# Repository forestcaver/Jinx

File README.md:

# Jinx

Eurorack 0603 triple S&amp;H in 4hp (based on the S&H section of Mutable Instruments Kinks module)

I have deleted the BoM which contained Mouser part numbers etc. as, despite requests here, I was receiveing far too many requests for part substitutions and advice on the BoM and build. Apologies to those who found it useful, but you can generate one from Eagle.

I have also deleted the gerber files as I also had complaints that they did not include the information that some people wanted (I generate a minimal silkscreen as I find on dense boards that a crowded silkscreen is confusing. As I am building just for me I don't think that is unreasonable. Also, it is trivial to generate gerbers with whatever information you need. So, to try to reduce the number of messages I receive about this, I have deleted them. Apologies to those who found them useful.

**** Please note - pcbs and panels are being sold by other people - I have no connection, financial or otherwise, to anyone selling pcbs and panels, hence I feel no commercial obligation to offer build support! I am just freely offering up these designs! Enjoy! ****

cc-by-sa-3.0

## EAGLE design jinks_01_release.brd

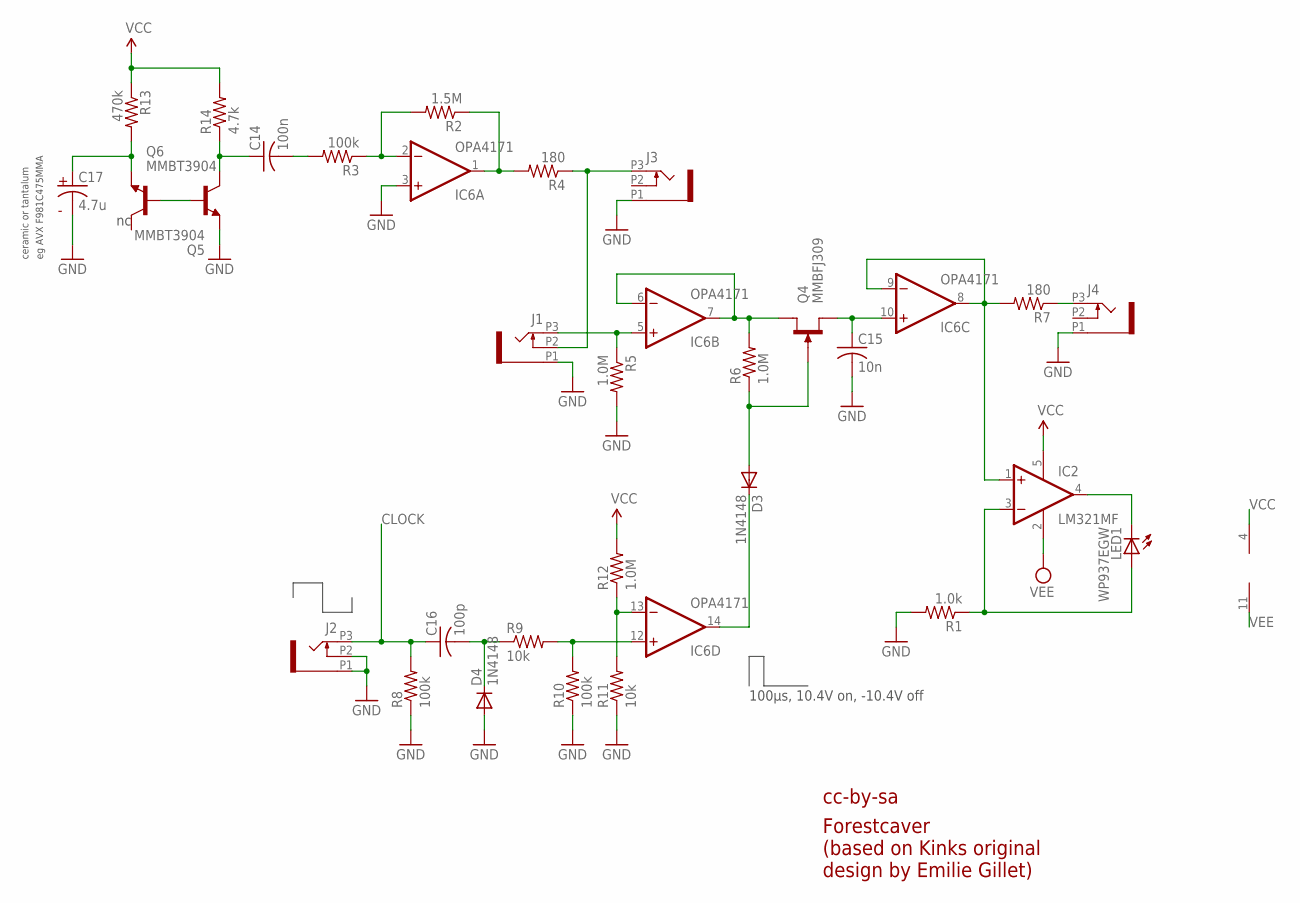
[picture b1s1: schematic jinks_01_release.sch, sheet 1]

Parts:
C14: 100n; C0603
C15: 10n; C0603
C16: 100p; C0603
C17: 4.7u; C0603
D3, D4: 1N4148; SOD523
IC2: LM321MF; SOT23-5
IC6: OPA4171; TSSOP14
J1, J2, J3, J4: PJ301_THONKICONN6; WQP_PJ_301M6
LED1: WP937EGW; LED3MM
Q4: MMBFJ309; SOT23
Q5, Q6: MMBT3904; SOT23-BEC
R1: 1.0k; R0603
R2: 1.5M; R0603
R3, R8, R10: 100k; R0603
R4, R7: 180; R0603
R5, R6, R12: 1.0M; R0603
R9, R11: 10k; R0603
R13: 470k; R0603
R14: 4.7k; R0603

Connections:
CLOCK: C16.1, J2.P3 (3), R8.2; also elsewhere on the board
GND: C15.2, C17.2, D4.A, IC6.3 (+IN), J1.P1 (1), J2.P1 (1), J2.P2 (2), J3.P1 (1), J4.P1 (1), Q6.E, R1.2, R5.2, R8.1, R10.1, R11.1; also elsewhere on the board
unnamed: IC2.4 (OUT), LED1.K (C)
unnamed: IC2.3 (-IN), LED1.A, R1.1
unnamed: IC2.1 (+IN), IC6.8 (OUT), IC6.9 (-IN), R7.2
unnamed: IC6.1 (OUT), R2.1, R4.2
unnamed: J1.P2 (2), J3.P3 (3), R4.1
unnamed: IC6.5 (+IN), J1.P3 (3), R5.1
unnamed: IC6.6 (-IN), IC6.7 (OUT), Q4.1 (D), R6.2
unnamed: D3.A, Q4.3 (G), R6.1
unnamed: D3.C, IC6.14 (OUT)
unnamed: C15.1, IC6.10 (+IN), Q4.2 (S)
unnamed: J4.P3 (3), R7.1
unnamed: C16.2, D4.C, R9.1
unnamed: IC6.12 (+IN), R9.2, R10.2
unnamed: IC6.13 (-IN), R11.2, R12.1
unnamed: C14.2, R3.2
unnamed: IC6.2 (-IN), R2.2, R3.1
unnamed: Q5.B, Q6.B
unnamed: C17.1, Q5.E, R13.2
unnamed: C14.1, Q6.C, R14.1
VCC: IC2.5 (V+), IC6.4 (V+), R12.2, R13.1, R14.2; also elsewhere on the board
VEE: IC2.2 (V-), IC6.11 (V-); also elsewhere on the board

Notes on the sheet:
cc-by-sa
100µs, 10.4V on, -10.4V off
eg AVX F981C475MMA
ceramic or tantalum
Forestcaver (based on Kinks original design by Emilie Gillet)

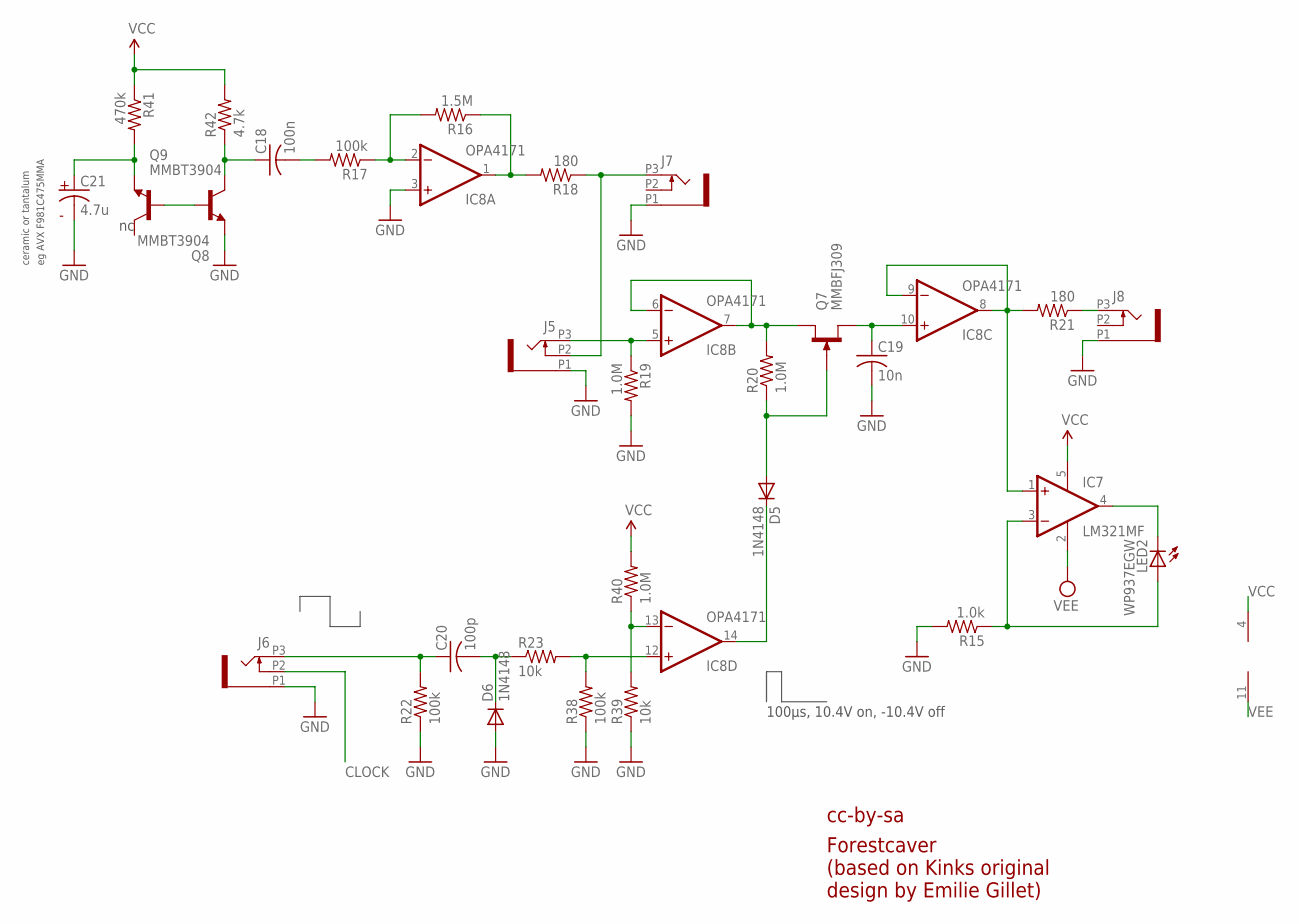
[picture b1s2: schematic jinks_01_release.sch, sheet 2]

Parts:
C18: 100n; C0603
C19: 10n; C0603
C20: 100p; C0603
C21: 4.7u; C0603
D5, D6: 1N4148; SOD523
IC7: LM321MF; SOT23-5
IC8: OPA4171; TSSOP14
J5, J6, J7, J8: PJ301_THONKICONN6; WQP_PJ_301M6
LED2: WP937EGW; LED3MM
Q7: MMBFJ309; SOT23
Q8, Q9: MMBT3904; SOT23-BEC
R15: 1.0k; R0603
R16: 1.5M; R0603
R17, R22, R38: 100k; R0603
R18, R21: 180; R0603
R19, R20, R40: 1.0M; R0603
R23, R39: 10k; R0603
R41: 470k; R0603
R42: 4.7k; R0603

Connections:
CLOCK: J6.P2 (2); also elsewhere on the board
GND: C19.2, C21.2, D6.A, IC8.3 (+IN), J5.P1 (1), J6.P1 (1), J7.P1 (1), J8.P1 (1), Q9.E, R15.2, R19.2, R22.1, R38.1, R39.1; also elsewhere on the board
unnamed: IC7.4 (OUT), LED2.K (C)
unnamed: IC7.3 (-IN), LED2.A, R15.1
unnamed: IC7.1 (+IN), IC8.8 (OUT), IC8.9 (-IN), R21.2
unnamed: IC8.1 (OUT), R16.1, R18.2
unnamed: J5.P2 (2), J7.P3 (3), R18.1
unnamed: IC8.5 (+IN), J5.P3 (3), R19.1
unnamed: IC8.6 (-IN), IC8.7 (OUT), Q7.1 (D), R20.2
unnamed: D5.A, Q7.3 (G), R20.1
unnamed: D5.C, IC8.14 (OUT)
unnamed: C19.1, IC8.10 (+IN), Q7.2 (S)
unnamed: J8.P3 (3), R21.1
unnamed: C20.1, J6.P3 (3), R22.2
unnamed: C20.2, D6.C, R23.1
unnamed: IC8.12 (+IN), R23.2, R38.2
unnamed: IC8.13 (-IN), R39.2, R40.1
unnamed: C18.2, R17.2
unnamed: IC8.2 (-IN), R16.2, R17.1
unnamed: Q8.B, Q9.B
unnamed: C21.1, Q8.E, R41.2
unnamed: C18.1, Q9.C, R42.1
VCC: IC7.5 (V+), IC8.4 (V+), R40.2, R41.1, R42.2; also elsewhere on the board
VEE: IC7.2 (V-), IC8.11 (V-); also elsewhere on the board

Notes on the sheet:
cc-by-sa
100µs, 10.4V on, -10.4V off
eg AVX F981C475MMA
ceramic or tantalum
Forestcaver (based on Kinks original design by Emilie Gillet)

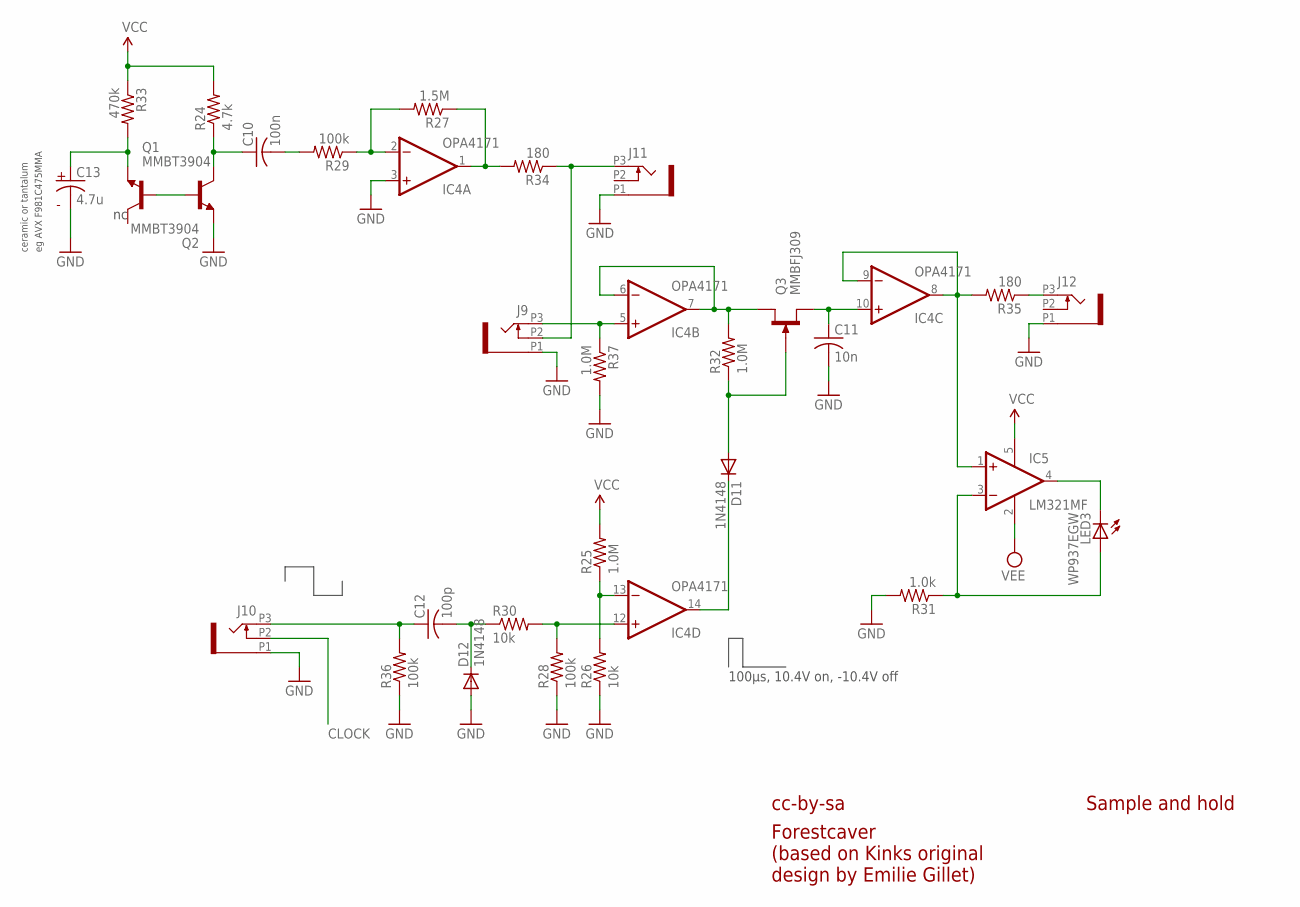
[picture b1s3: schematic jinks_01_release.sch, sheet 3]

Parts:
C10: 100n; C0603
C11: 10n; C0603
C12: 100p; C0603
C13: 4.7u; C0603
D11, D12: 1N4148; SOD523
IC4: OPA4171; TSSOP14
IC5: LM321MF; SOT23-5
J9, J10, J11, J12: PJ301_THONKICONN6; WQP_PJ_301M6
LED3: WP937EGW; LED3MM
Q1, Q2: MMBT3904; SOT23-BEC
Q3: MMBFJ309; SOT23
R24: 4.7k; R0603
R25, R32, R37: 1.0M; R0603
R26, R30: 10k; R0603
R27: 1.5M; R0603
R28, R29, R36: 100k; R0603
R31: 1.0k; R0603
R33: 470k; R0603
R34, R35: 180; R0603

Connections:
CLOCK: J10.P2 (2); also elsewhere on the board
GND: C11.2, C13.2, D12.A, IC4.3 (+IN), J9.P1 (1), J10.P1 (1), J11.P1 (1), J12.P1 (1), Q1.E, R26.1, R28.1, R31.2, R36.1, R37.2; also elsewhere on the board
unnamed: IC4.8 (OUT), IC4.9 (-IN), IC5.1 (+IN), R35.2
unnamed: Q1.B, Q2.B
unnamed: C13.1, Q2.E, R33.2
unnamed: C10.2, R29.2
unnamed: IC4.2 (-IN), R27.2, R29.1
unnamed: IC5.3 (-IN), LED3.A, R31.1
unnamed: IC5.4 (OUT), LED3.K (C)
unnamed: C10.1, Q1.C, R24.1
unnamed: IC4.1 (OUT), R27.1, R34.2
unnamed: J9.P2 (2), J11.P3 (3), R34.1
unnamed: IC4.5 (+IN), J9.P3 (3), R37.1
unnamed: IC4.6 (-IN), IC4.7 (OUT), Q3.1 (D), R32.2
unnamed: D11.A, Q3.3 (G), R32.1
unnamed: D11.C, IC4.14 (OUT)
unnamed: C11.1, IC4.10 (+IN), Q3.2 (S)
unnamed: IC4.12 (+IN), R28.2, R30.2
unnamed: J12.P3 (3), R35.1
unnamed: C12.1, J10.P3 (3), R36.2
unnamed: IC4.13 (-IN), R25.1, R26.2
unnamed: C12.2, D12.C, R30.1
VCC: IC5.5 (V+), R24.2, R25.2, R33.1; also elsewhere on the board
VEE: IC5.2 (V-); also elsewhere on the board

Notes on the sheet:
cc-by-sa
Sample and hold
100µs, 10.4V on, -10.4V off
eg AVX F981C475MMA
ceramic or tantalum
Forestcaver (based on Kinks original design by Emilie Gillet)

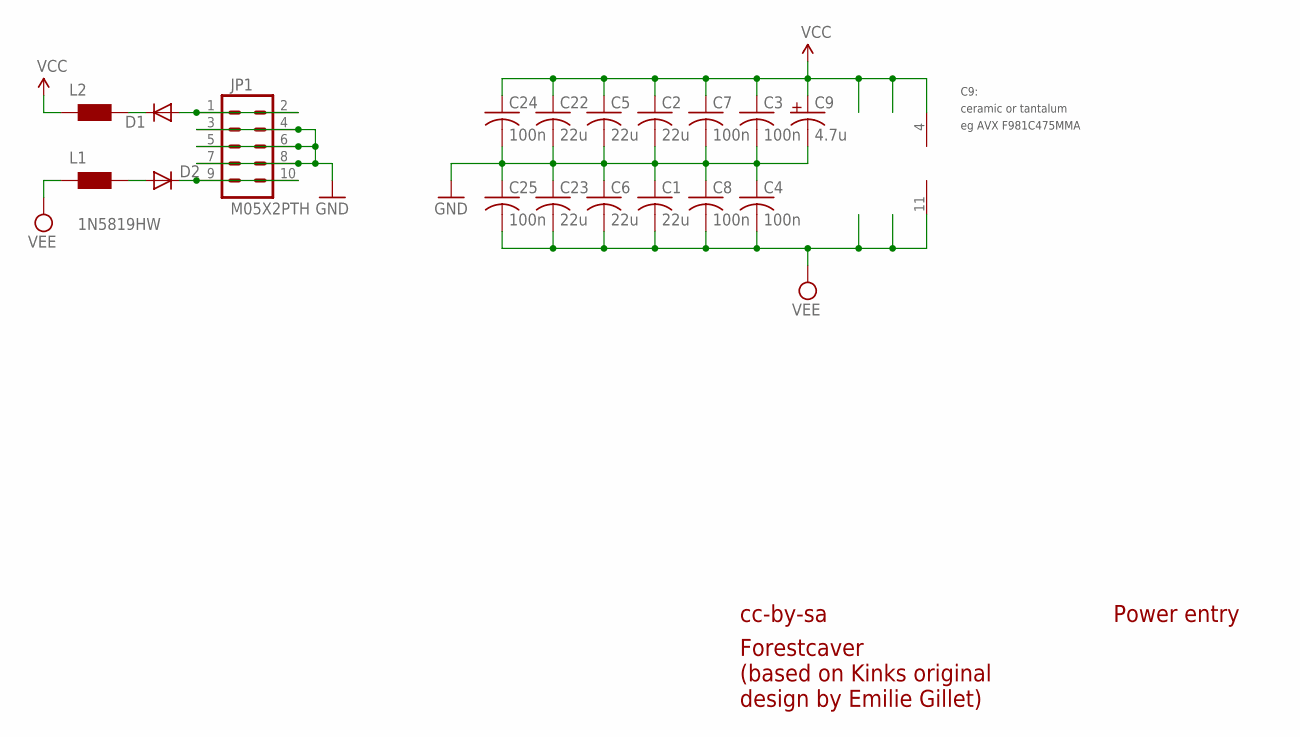
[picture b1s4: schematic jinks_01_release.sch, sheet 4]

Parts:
C1, C2, C5, C6, C22, C23: 22u; C0805
C3, C4, C7, C8, C24, C25: 100n; C0603
C9: 4.7u; C0603
D1, D2: 1N5819HW; SOD123
IC4: OPA4171; TSSOP14
JP1: M05X2PTH; AVR_ICSP
L1, L2: WE-CBF_0603; 0603

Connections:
GND: C1.1, C2.2, C3.2, C4.1, C5.2, C6.1, C7.2, C8.1, C9.2, C22.2, C23.1, C24.2, C25.1, JP1.3, JP1.4, JP1.5, JP1.6, JP1.7, JP1.8; also elsewhere on the board
unnamed: D1.A, JP1.1, JP1.2
unnamed: D2.C, JP1.9, JP1.10
unnamed: D1.C, L2.2
unnamed: D2.A, L1.2
VCC: C2.1, C3.1, C5.1, C7.1, C9.1, C22.1, C24.1, IC4.4 (V+), L2.1; also elsewhere on the board
VEE: C1.2, C4.2, C6.2, C8.2, C23.2, C25.2, IC4.11 (V-), L1.1; also elsewhere on the board

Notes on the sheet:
cc-by-sa
Power entry
eg AVX F981C475MMA
ceramic or tantalum
C9:
Forestcaver (based on Kinks original design by Emilie Gillet)

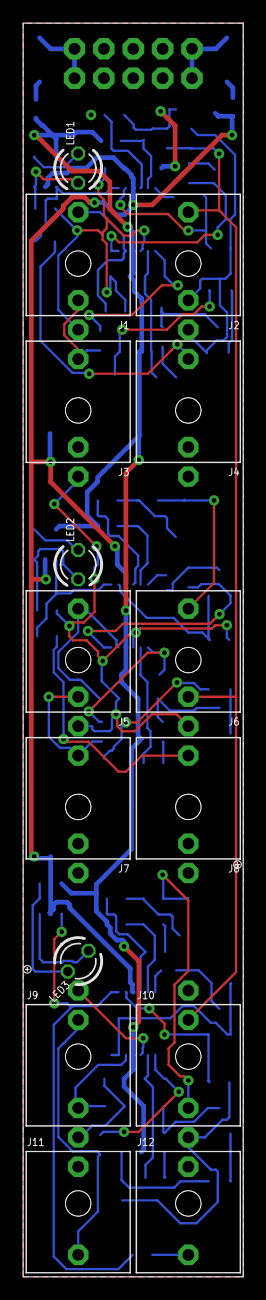
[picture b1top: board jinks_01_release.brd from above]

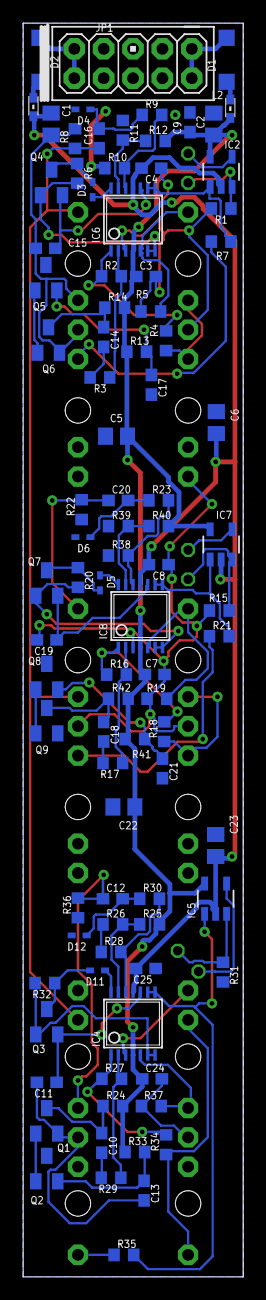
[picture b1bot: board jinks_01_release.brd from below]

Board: 2 copper layers, 19.0 x 108.4 mm, 108 parts (93 on the bottom side), 67 nets.

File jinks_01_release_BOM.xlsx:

jinks_01_release
Qty | Value | Device | Package | Parts | Description | Mouser Part Number
2 |  | WE-CBF_0603 | 603 | L1, L2 | SMD EMI Suppression Ferrite Beads | 710-742792664
9 | 1.0M | R-US_R0603 | R0603 | R5, R6, R12, R19, R20, R25, R32, R37, R40 | RESISTOR, American symbol | 667-ERJ-3EKF1004V
3 | 1.0k | R-US_R0603 | R0603 | R1, R15, R31 | RESISTOR, American symbol | 667-ERJ-3EKF1001V
3 | 1.5M | R-US_R0603 | R0603 | R2, R16, R27 | RESISTOR, American symbol | 667-ERJ-3EKF1504V
9 | 100k | R-US_R0603 | R0603 | R3, R8, R10, R17, R22, R28, R29, R36, R38 | RESISTOR, American symbol | 667-ERJ-3EKF1003V
9 | 100n | C-USC0603 | C0603 | C3, C4, C7, C8, C10, C14, C18, C24, C25 | CAPACITOR, American symbol | 81-GRM188R71E104JA1J
3 | 100p | C-USC0603 | C0603 | C12, C16, C20 | CAPACITOR, American symbol | 81-GRM1885C2A101JA01
6 | 10k | R-US_R0603 | R0603 | R9, R11, R23, R26, R30, R39 | RESISTOR, American symbol | 667-ERJ-3EKF1002V
3 | 10n | C-USC0603 | C0603 | C11, C15, C19 | CAPACITOR, American symbol | 81-GRM18R71H103JA01D
6 | 180 | R-US_R0603 | R0603 | R4, R7, R18, R21, R34, R35 | RESISTOR, American symbol | 667-ERJ-3EKF1800V
6 | 1N4148 | DIODE-SOD523 | SOD523 | D3, D4, D5, D6, D11, D12 | DIODE | 512-1N4148WT
2 | 1N5819HW | DIODE-SOD123 | SOD123 | D1, D2 | DIODE | 621-1N5819HW-F
6 | 22u | C-USC0805 | C0805 | C1, C2, C5, C6, C22, C23 | CAPACITOR, American symbol | 81-GRM21BR61E226ME4L
3 | 4.7k | R-US_R0603 | R0603 | R14, R24, R42 | RESISTOR, American symbol | 667-ERJ-3EKF4701V
4 | 4.7u | C-USC0603 | C0603 | C9, C13, C17, C21 | CAPACITOR, American symbol | AVX F981C475MMA
3 | 470k | R-US_R0603 | R0603 | R13, R33, R41 | RESISTOR, American symbol | 667-ERJ-3EKF4703V
3 | LM321MF | LM321MF | SOT23-5 | IC2, IC5, IC7 | Low Power Single Op Amp | 926-LM321MFX/NOPB
1 | M05X2PTH | M05X2PTH | AVR_ICSP | JP1 | Header 5x2 | 649-67996-410HLF
3 | MMBFJ309 | MMBFJ3 | SOT23 | Q3, Q4, Q7 | N-Channel RF Amplifier | 512-MMBFJ309
6 | MMBT3904 | MMBT3904LT1-NPN-SOT23-BEC | SOT23-BEC | Q1, Q2, Q5, Q6, Q8, Q9 | NPN Transistror | 863-MMBT3904LT1G
3 | OPA4171 | TL074PW | TSSOP14 | IC4, IC6, IC8 | OP AMP | 595-OPA4171AIPW
12 | PJ301_THONKICONN6 | PJ301_THONKICONN6 | WQP_PJ_301M6 | J1, J2, J3, J4, J5, J6, J7, J8, J9, J10, J11, J12
3 | WP937EGW | LED3MM | LED3MM | LED1, LED2, LED3 | LED | 604-WP937EGW

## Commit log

2019-06-24 Add files via upload
    BOM
2019-09-10 Updated bom to clarify mlcc cap ok instead of tant
    Added an explicit mouser part # for ceramic caps to make it clearer mlcc cap is ok instead of tantalum
2020-10-01 BoM deleted due to inability to the number of requests for support and alternative Mouser part numbers
2020-10-01 Removed gerbers due to requests for differering alternative information on silkscreen. Please generate your own.

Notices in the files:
jinks_01_release.brd:
Jinx 1.0, CC-By-SA, 2019 Forestcaver
